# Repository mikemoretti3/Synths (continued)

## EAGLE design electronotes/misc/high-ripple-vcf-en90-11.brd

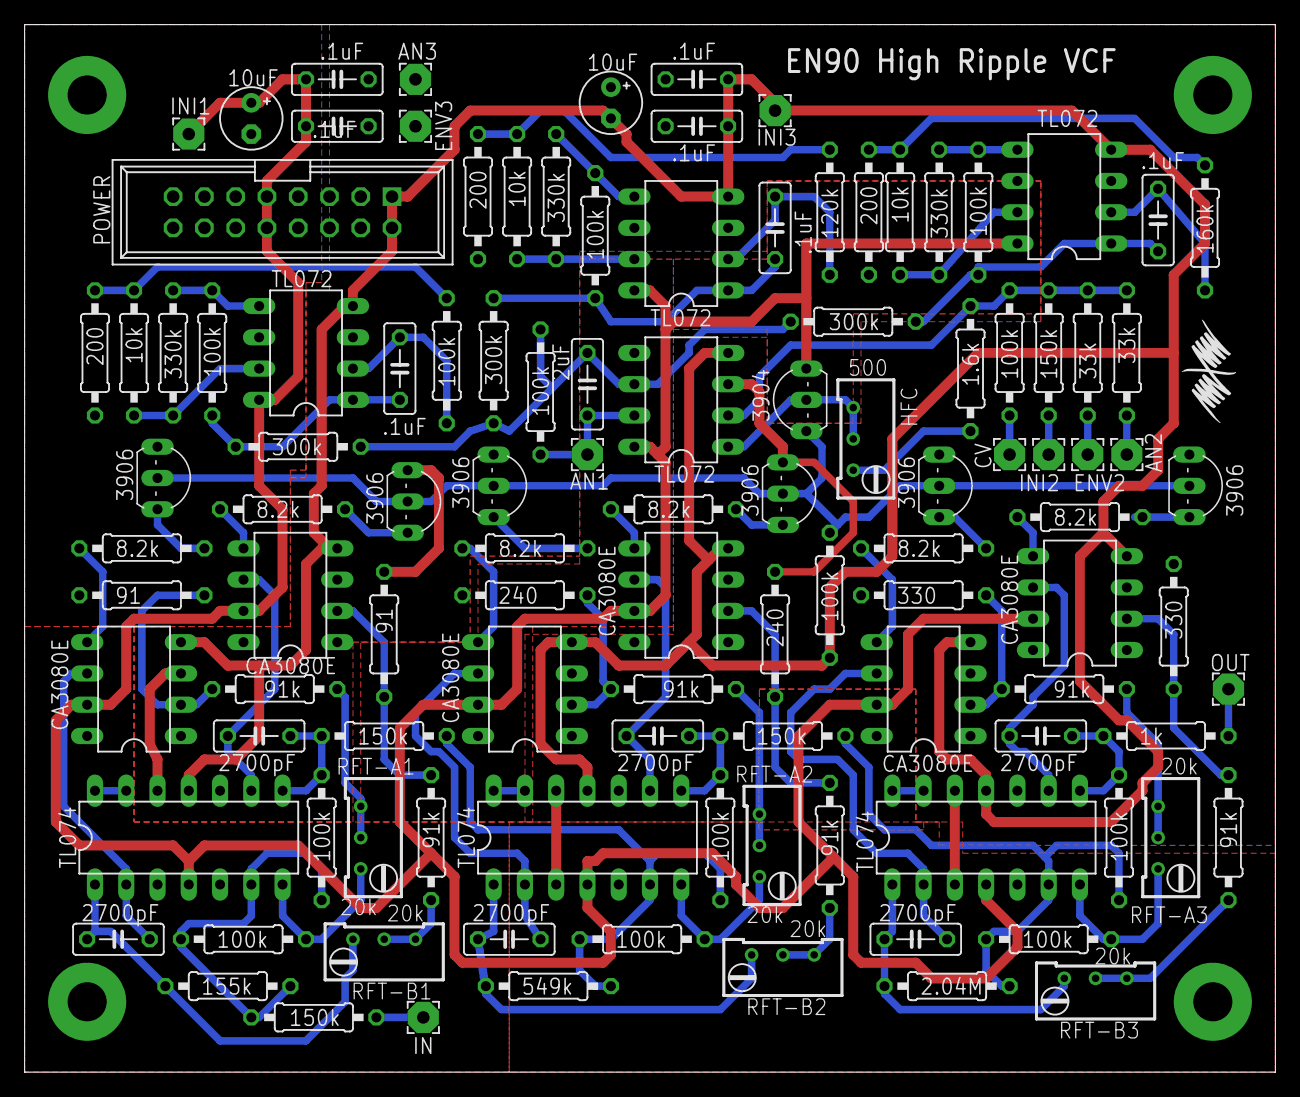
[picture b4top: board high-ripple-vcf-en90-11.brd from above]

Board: 2 copper layers, 101.6 x 85.1 mm, 111 parts (0 on the bottom side), 75 nets.

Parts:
AN1, AN2, AN3: 2,54/1,0
C1, C2, C3, C4, C9, C11, C12: .1uF; C050-025X075
C5, C6: 10uF; E2,5-5
C7, C8, C13, C14, C15, C16: 2700pF; C050-025X075
C10: 2uF; C050-025X075
CV: 2,54/1,0
ENV2, ENV3: 2,54/1,0
HFC: 500; RTRIM64W
IC1, IC8, IC11: TL074; DIL14
IC2, IC3, IC6, IC7: TL072; DIL08
IC4, IC5, IC9, IC10, IC12, IC13: CA3080E; DIL08
IN: 2,54/1,0
INI1, INI2, INI3: 2,54/1,0
OUT: 2,54/1,0
POWER: EURORACK-POWER; PINSHRD_PTH_2X8
R1, R12, R14, R16, R19, R20, R25, R29, R34, R39, R41, R44: 100k; 0207/10
R2, R13, R17, R40: 150k; 0207/10
R3, R5: 33k; 0207/10
R4: 1.6k; 0207/10
R6, R7, R8, R9, R10, R11: 8.2k; 0207/10
R15, R18, R27, R28, R42, R43: 91k; 0207/10
R21, R30, R35: 330k; 0207/10
R22, R31, R36: 10k; 0207/10
R23, R32, R37: 200; 0207/10
R24, R33, R38: 300k; 0207/10
R45: 1k; 0207/10
RA-A1: 91; 0207/10
RA-A2: 240; 0207/10
RA-A3: 330; 0207/10
RA-B1: 91; 0207/10
RA-B2: 240; 0207/10
RA-B3: 330; 0207/10
RFT-A1, RFT-A2, RFT-A3: 20k; RTRIM64W
RFT-B1, RFT-B2, RFT-B3: 20k; RTRIM64W
RQ1: 155k; 0207/10
RQ2: 549k; 0207/10
RQ3: 2.04M; 0207/10
RT1: 100k; 0207/10
RT2: 120k; 0207/10
RT3: 160k; 0207/10
T1: 3904; TO92-EBC
T2, T3, T4, T5, T6, T7: 3906; TO92-EBC

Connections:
+12V: C1.1, C3.1, C5.+, IC1.4, IC2.8, IC3.8, IC4.7, IC5.7, IC6.8, IC7.8, IC8.4, IC9.7, IC10.7, IC11.4, IC12.7, IC13.7, INI1.1, POWER.+12V@1, POWER.+12V@2, T1.C
-12V: C2.2, C4.2, C6.-, IC1.11, IC2.4, IC3.4, IC4.4, IC5.4, IC6.4, IC7.4, IC8.11, IC9.4, IC10.4, IC11.11, IC12.4, IC13.4, INI3.1, POWER.-12V@1, POWER.-12V@2, R12.1
A: IC4.5, R6.1
B: IC5.5, R7.1
C: IC9.5, R8.1
D: IC10.5, R9.1
E: IC12.5, R10.1
GND: AN3.1, C1.2, C2.1, C3.2, C4.1, C5.-, C6.+, ENV3.1, IC1.3, IC1.5, IC1.10, IC1.12, IC2.3, IC2.5, IC3.3, IC3.6, IC4.3, IC5.3, IC6.3, IC6.6, IC7.3, IC7.6, IC8.3, IC8.5, IC8.10, IC8.12, IC9.3, IC10.3, IC11.3, IC11.5, IC11.10, IC11.12, IC12.3, IC13.3, POWER.GND@1, POWER.GND@2, POWER.GND@3, POWER.GND@4, POWER.GND@5, POWER.GND@6, R23.2, R32.2, R37.2, RA-A1.1, RA-A2.1, RA-A3.1, RA-B1.1, RA-B2.1, RA-B3.1, T2.E, T3.E, T4.E, T5.E, T6.E, T7.E
unnamed: C10.1, IC2.6, R24.2, R25.1, R33.2, R38.2
unnamed: CV.1, R1.1
unnamed: INI2.1, R2.1
unnamed: ENV2.1, R3.1
unnamed: AN2.1, R5.2
unnamed: IC2.2, R1.2, R2.2, R3.2, R4.1, R5.1
unnamed: HFC.3, R4.2
unnamed: HFC.1, HFC.2, IC2.1, T1.B
unnamed: R12.2, T1.E, T2.B, T3.B, T4.B, T5.B, T6.B, T7.B
unnamed: R6.2, T2.C
unnamed: R7.2, T3.C
unnamed: R8.2, T4.C
unnamed: R9.2, T5.C
unnamed: R10.2, T6.C
unnamed: R11.2, T7.C
unnamed: C9.2, IC3.1, R20.2, R24.1
unnamed: IC3.5, R20.1, R21.2
unnamed: IC3.7, R21.1, R22.2
unnamed: R22.1, R23.1, RT1.2
unnamed: C11.2, IC6.1, R29.2, R33.1
unnamed: C9.1, IC3.2, RT1.1
unnamed: IC6.5, R29.1, R30.2
unnamed: IC6.7, R30.1, R31.2
unnamed: R31.1, R32.1, RT2.2
unnamed: C11.1, IC6.2, RT2.1
unnamed: C12.2, IC7.1, R34.2, R38.1
unnamed: IC7.5, R34.1, R35.2
unnamed: IC7.7, R35.1, R36.2
unnamed: R36.1, R37.1, RT3.2
unnamed: C12.1, IC7.2, RT3.1
unnamed: C8.2, IC1.8, R16.1, R17.1
unnamed: IC8.7, R19.2, RFT-A2.3
unnamed: R27.1, RFT-A2.1, RFT-A2.2
unnamed: IC9.2, R27.2, RA-A2.2
unnamed: C13.1, IC8.2, IC9.6
unnamed: IC1.7, R14.2, RFT-A1.3
unnamed: R15.1, RFT-A1.1, RFT-A1.2
unnamed: IC4.2, R15.2, RA-A1.2
unnamed: C7.1, IC1.2, IC4.6
unnamed: C7.2, IC1.1, RFT-B1.3, RQ1.1
unnamed: C13.2, IC8.1, RFT-B2.3, RQ2.1
unnamed: R18.2, RFT-B1.1, RFT-B1.2
unnamed: IC5.2, R18.1, RA-B1.2
unnamed: C8.1, IC1.9, IC5.6
unnamed: IC1.6, R13.2, R14.1, R16.2, RQ1.2
unnamed: IC1.13, IC1.14
unnamed: R28.2, RFT-B2.1, RFT-B2.2
unnamed: IC10.2, R28.1, RA-B2.2
unnamed: C14.1, IC8.9, IC10.6
unnamed: IC8.6, R17.2, R19.1, R39.2, RQ2.2
unnamed: IC8.13, IC8.14
unnamed: C14.2, IC8.8, R39.1, R40.1
unnamed: IC11.7, R41.2, RFT-A3.3
unnamed: R42.1, RFT-A3.1, RFT-A3.2
unnamed: IC12.2, R42.2, RA-A3.2
unnamed: C15.1, IC11.2, IC12.6
unnamed: C15.2, IC11.1, RFT-B3.3, RQ3.1
unnamed: R43.2, RFT-B3.1, RFT-B3.2
unnamed: IC13.2, R43.1, RA-B3.2
unnamed: C16.1, IC11.9, IC13.6
unnamed: IC11.6, R40.2, R41.1, R44.2, RQ3.2
unnamed: IC11.13, IC11.14
unnamed: C16.2, IC11.8, R44.1, R45.1
unnamed: IN.1, R13.1
unnamed: OUT.1, R45.2
unnamed: IC13.5, R11.1
X: AN1.1, C10.2, IC2.7, R25.2

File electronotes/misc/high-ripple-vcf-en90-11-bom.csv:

Qty,Value,Device,Package,Parts,Description
7,.1uF,C-US050-025X075,C050-025X075,"C1, C2, C3, C4, C9, C11, C12","CAPACITOR, American symbol"
6,2700pF,C-US050-025X075,C050-025X075,"C7, C8, C13, C14, C15, C16","CAPACITOR, American symbol"
1,2uF,C-US050-025X075,C050-025X075,C10,"CAPACITOR, American symbol"
2,10uF,CPOL-USE2.5-5,"E2,5-5","C5, C6","POLARIZED CAPACITOR, American symbol"
2,91,R-US_0207/10,0207/10,"RA-A1, RA-B1","RESISTOR, American symbol"
3,200,R-US_0207/10,0207/10,"R23, R32, R37","RESISTOR, American symbol"
2,240,R-US_0207/10,0207/10,"RA-A2, RA-B2","RESISTOR, American symbol"
2,330,R-US_0207/10,0207/10,"RA-A3, RA-B3","RESISTOR, American symbol"
1,1k,R-US_0207/10,0207/10,R45,"RESISTOR, American symbol"
1,1.6k,R-US_0207/10,0207/10,R4,"RESISTOR, American symbol"
6,8.2k,R-US_0207/10,0207/10,"R6, R7, R8, R9, R10, R11","RESISTOR, American symbol"
3,10k,R-US_0207/10,0207/10,"R22, R31, R36","RESISTOR, American symbol"
6,20k,R-TRIMM64W,RTRIM64W,"RFT-A1, RFT-A2, RFT-A3, RFT-B1, RFT-B2, RFT-B3",Trimm resistor
2,33k,R-US_0207/10,0207/10,"R3, R5","RESISTOR, American symbol"
6,91k,R-US_0207/10,0207/10,"R15, R18, R27, R28, R42, R43","RESISTOR, American symbol"
13,100k,R-US_0207/10,0207/10,"R1, R12, R14, R16, R19, R20, R25, R29, R34, R39, R41, R44, RT1","RESISTOR, American symbol"
1,120k,R-US_0207/10,0207/10,RT2,"RESISTOR, American symbol"
4,150k,R-US_0207/10,0207/10,"R2, R13, R17, R40","RESISTOR, American symbol"
1,155k,R-US_0207/10,0207/10,RQ1,"RESISTOR, American symbol"
1,160k,R-US_0207/10,0207/10,RT3,"RESISTOR, American symbol"
1,2.04M,R-US_0207/10,0207/10,RQ3,"RESISTOR, American symbol"
3,300k,R-US_0207/10,0207/10,"R24, R33, R38","RESISTOR, American symbol"
3,330k,R-US_0207/10,0207/10,"R21, R30, R35","RESISTOR, American symbol"
1,549k,R-US_0207/10,0207/10,RQ2,"RESISTOR, American symbol"
1,3904,2N3904-NPN-TO92-EBC,TO92-EBC,T1,NPN Transistror
6,3906,2N3906-PNP-TO92-EBC,TO92-EBC,"T2, T3, T4, T5, T6, T7",PNP Transistror
1,500,R-TRIMM64W,RTRIM64W,HFC,Trimm resistor
6,CA3080E,CA3080E,DIL08,"IC4, IC5, IC9, IC10, IC12, IC13",OTA
4,TL072,TL072-TOPP,DIL08,"IC2, IC3, IC6, IC7",OP AMP
3,TL074,TL074-TOPP,DIL14,"IC1, IC8, IC11",OP AMP
1,EURORACK-POWER,EURORACK-POWER,PINSHRD_PTH_2X8,POWER,

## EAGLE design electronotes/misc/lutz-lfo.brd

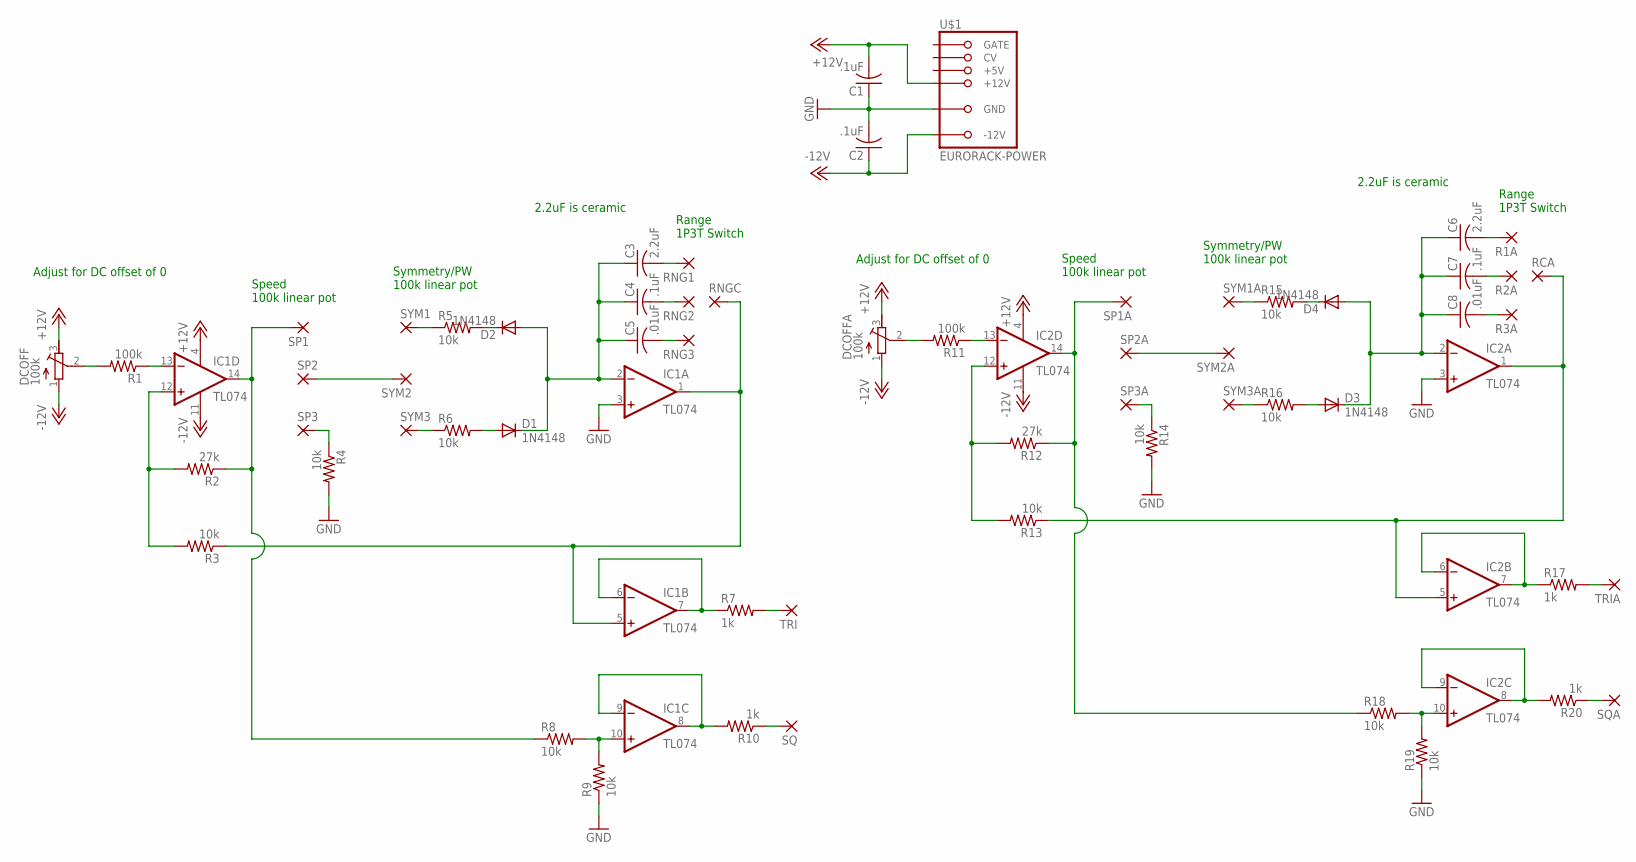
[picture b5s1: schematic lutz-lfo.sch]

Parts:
C1, C2, C4, C7: .1uF; C050-025X075
C3, C6: 2.2uF; C050-025X075
C5, C8: .01uF; C050-025X075
D1, D2, D3, D4: 1N4148; DO35-7
DCOFF: 100k; RTRIM64Y
DCOFFA: 100k; RTRIM64Y
IC1, IC2: TL074; DIL14
R1, R11: 100k; 0207/10
R1A, R2A, R3A: 2,54/1,0
R2, R12: 27k; 0207/10
R3, R4, R5, R6, R8, R9, R13, R14, R15, R16, R18, R19: 10k; 0207/10
R7, R10, R17, R20: 1k; 0207/10
RCA: 2,54/1,0
RNG1, RNG2, RNG3: 2,54/1,0
RNGC: 2,54/1,0
SP1, SP1A, SP2, SP2A, SP3, SP3A: 2,54/1,0
SQ: 2,54/1,0
SQA: 2,54/1,0
SYM1, SYM1A, SYM2, SYM2A, SYM3, SYM3A: 2,54/1,0
TRI: 2,54/1,0
TRIA: 2,54/1,0
U$1: EURORACK-POWER; PINSHRD_PTH_2X8

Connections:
+12V: C1.2, DCOFF.3 (E), DCOFFA.3 (E), IC1.4 (V+), IC2.4 (V+), U$1.+12V@1 (+12V), U$1.+12V@2 (+12V)
-12V: C2.1, DCOFF.1 (A), DCOFFA.1 (A), IC1.11 (V-), IC2.11 (V-), U$1.-12V@1 (-12V), U$1.-12V@2 (-12V)
GND: C1.1, C2.2, IC1.3 (+IN), IC2.3 (+IN), R4.2, R9.1, R14.2, R19.1, U$1.GND@1 (GND), U$1.GND@2 (GND), U$1.GND@3 (GND), U$1.GND@4 (GND), U$1.GND@5 (GND), U$1.GND@6 (GND)
unnamed: DCOFF.2 (S), R1.2
unnamed: IC1.13 (-IN), R1.1
unnamed: IC1.12 (+IN), R2.2, R3.2
unnamed: IC1.14 (OUT), R2.1, R8.1, SP1.1
unnamed: R4.1, SP3.1
unnamed: R5.1, SYM1.1
unnamed: R6.1, SYM3.1
unnamed: SP2.1, SYM2.1
unnamed: D2.C, R5.2
unnamed: D1.A, R6.2
unnamed: C3.1, C4.1, C5.1, D1.C, D2.A, IC1.2 (-IN)
unnamed: C5.2, RNG3.1
unnamed: C4.2, RNG2.1
unnamed: C3.2, RNG1.1
unnamed: IC1.1 (OUT), IC1.5 (+IN), R3.1, RNGC.1
unnamed: IC1.6 (-IN), IC1.7 (OUT), R7.1
unnamed: DCOFFA.2 (S), R11.2
unnamed: IC1.8 (OUT), IC1.9 (-IN), R10.2
unnamed: R7.2, TRI.1
unnamed: R10.1, SQ.1
unnamed: IC1.10 (+IN), R8.2, R9.2
unnamed: IC2.13 (-IN), R11.1
unnamed: IC2.12 (+IN), R12.2, R13.2
unnamed: R14.1, SP3A.1
unnamed: R15.1, SYM1A.1
unnamed: R16.1, SYM3A.1
unnamed: SP2A.1, SYM2A.1
unnamed: D4.C, R15.2
unnamed: D3.A, R16.2
unnamed: C6.1, C7.1, C8.1, D3.C, D4.A, IC2.2 (-IN)
unnamed: C8.2, R3A.1
unnamed: C7.2, R2A.1
unnamed: C6.2, R1A.1
unnamed: IC2.1 (OUT), IC2.5 (+IN), R13.1, RCA.1
unnamed: IC2.6 (-IN), IC2.7 (OUT), R17.1
unnamed: IC2.8 (OUT), IC2.9 (-IN), R20.2
unnamed: R17.2, TRIA.1
unnamed: R20.1, SQA.1
unnamed: IC2.10 (+IN), R18.2, R19.2
unnamed: IC2.14 (OUT), R12.1, R18.1, SP1A.1

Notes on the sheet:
Speed 100k linear pot
Symmetry/PW 100k linear pot
Range 1P3T Switch
2.2uF is ceramic
Adjust for DC offset of 0

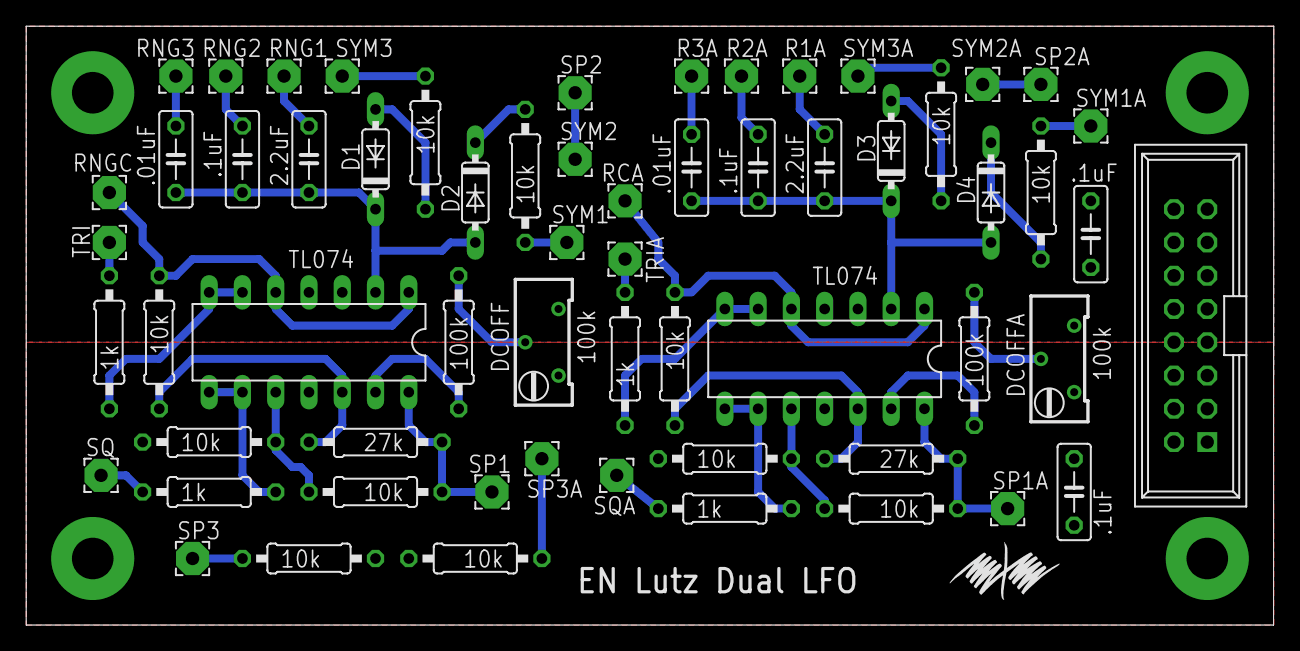
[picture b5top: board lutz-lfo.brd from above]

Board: 2 copper layers, 95.2 x 45.7 mm, 61 parts (0 on the bottom side), 43 nets.

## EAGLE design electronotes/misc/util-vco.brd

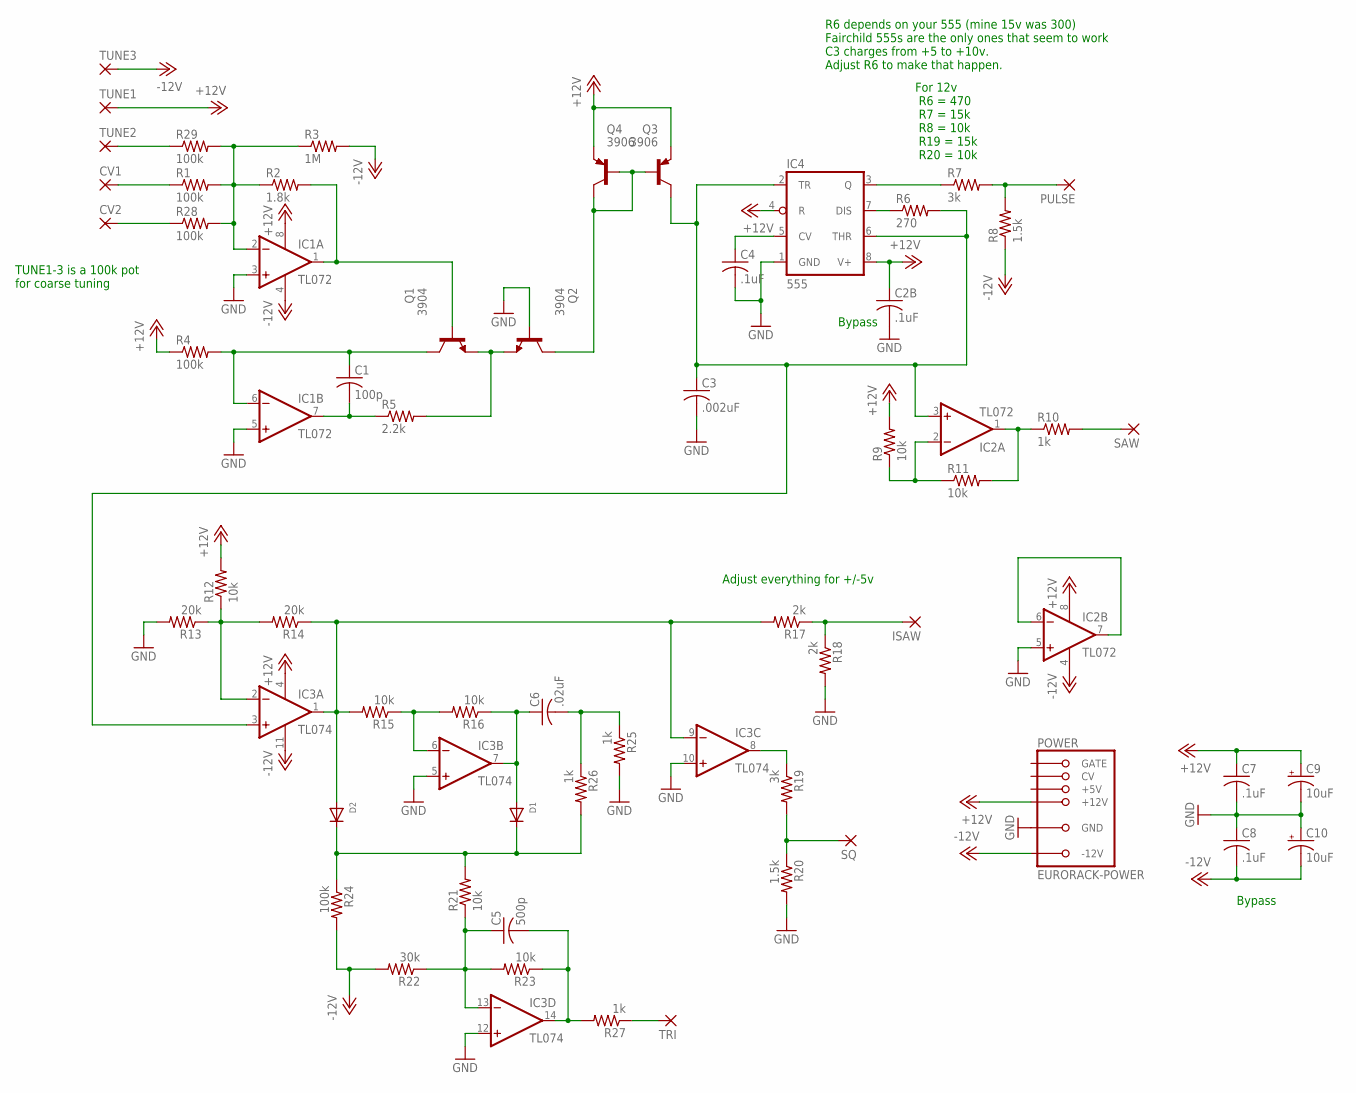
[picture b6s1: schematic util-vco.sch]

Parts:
C1: 100p; C050-025X075
C2B, C4, C7, C8: .1uF; C050-025X075
C3: .002uF; C050-025X075
C5: 500p; C050-025X075
C6: .02uF; C050-025X075
C9, C10: 10uF; E2,5-5
CV1, CV2: 2,54/1,0
D1, D2: DIODEDO-1N4148; DO-1N4148
IC1, IC2: TL072; DIL08
IC3: TL074; DIL14
IC4: 555; DIL08
ISAW: 2,54/1,0
POWER: EURORACK-POWER; PINSHRD_PTH_2X8
PULSE: 2,54/1,0
Q1, Q2: 3904; TO92
Q3, Q4: 3906; TO92
R1, R4, R24, R28, R29: 100k; 0207/10
R2: 1.8k; 0207/10
R3: 1M; 0207/10
R5: 2.2k; 0207/10
R6: 270; 0207/10
R7, R19: 3k; 0207/10
R8, R20: 1.5k; 0207/10
R9, R11, R12, R15, R16, R21, R23: 10k; 0207/10
R10, R25, R26, R27: 1k; 0207/10
R13, R14: 20k; 0207/10
R17, R18: 2k; 0207/10
R22: 30k; 0207/10
SAW: 2,54/1,0
SQ: 2,54/1,0
TRI: 2,54/1,0
TUNE1, TUNE2, TUNE3: 2,54/1,0

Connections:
+12V: C2B.1, C7.1, C9.+, IC1.8 (V+), IC2.8 (V+), IC3.4 (V+), IC4.4 (R), IC4.8 (V+), POWER.+12V@1 (+12V), POWER.+12V@2 (+12V), Q3.3 (E), Q4.3 (E), R4.1, R9.2, R12.2, TUNE1.1
-12V: C8.2, C10.-, IC1.4 (V-), IC2.4 (V-), IC3.11 (V-), POWER.-12V@1 (-12V), POWER.-12V@2 (-12V), R3.2, R8.1, R22.2, R24.2, TUNE3.1
GND: C2B.2, C3.2, C4.2, C7.2, C8.1, C9.-, C10.+, IC1.3 (+IN), IC1.5 (+IN), IC2.5 (+IN), IC3.5 (+IN), IC3.10 (+IN), IC3.12 (+IN), IC4.1 (GND), POWER.GND@1 (GND), POWER.GND@2 (GND), POWER.GND@3 (GND), POWER.GND@4 (GND), POWER.GND@5 (GND), POWER.GND@6 (GND), Q2.2 (B), R13.2, R18.2, R20.2, R25.2
unnamed: IC1.2 (-IN), R1.2, R2.1, R3.1, R28.2, R29.2
unnamed: IC1.1 (OUT), Q1.2 (B), R2.2
unnamed: C1.1, IC1.6 (-IN), Q1.1 (C), R4.2
unnamed: C1.2, IC1.7 (OUT), R5.1
unnamed: Q1.3 (E), Q2.3 (E), R5.2
unnamed: C4.1, IC4.5 (CV)
unnamed: Q2.1 (C), Q3.1 (C), Q3.2 (B), Q4.2 (B)
unnamed: D2.A, IC3.1 (OUT), IC3.9 (-IN), R14.1, R15.2, R17.2
unnamed: IC4.3 (Q), R7.1
unnamed: PULSE.1, R7.2, R8.2
unnamed: IC2.6 (-IN), IC2.7 (OUT)
unnamed: IC4.7 (DIS), R6.1
unnamed: IC3.6 (-IN), R15.1, R16.2
unnamed: C6.1, D1.A, IC3.7 (OUT), R16.1
unnamed: IC2.2 (-IN), R9.1, R11.1
unnamed: IC2.1 (OUT), R10.1, R11.2
unnamed: R10.2, SAW.1
unnamed: IC3.2 (-IN), R12.1, R13.1, R14.2
unnamed: C3.1, IC2.3 (+IN), IC3.3 (+IN), IC4.2 (TR), IC4.6 (THR), Q4.1 (C), R6.2
unnamed: C6.2, R25.1, R26.1
unnamed: D1.C, D2.C, R21.2, R24.1, R26.2
unnamed: C5.1, IC3.13 (-IN), R21.1, R22.1, R23.2
unnamed: C5.2, IC3.14 (OUT), R23.1, R27.2
unnamed: R27.1, TRI.1
unnamed: ISAW.1, R17.1, R18.1
unnamed: IC3.8 (OUT), R19.1
unnamed: R19.2, R20.1, SQ.1
unnamed: CV2.1, R28.1
unnamed: R29.1, TUNE2.1
unnamed: CV1.1, R1.1

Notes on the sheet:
Bypass
TUNE1-3 is a 100k pot for coarse tuning
Adjust everything for +/-5v
For 12v R6 = 470 R7 = 15k R8 = 10k R19 = 15k R20 = 10k
R6 depends on your 555 (mine 15v was 300) Fairchild 555s are the only ones that seem to work C3 charges from +5 to +10v. Adjust R6 to make that happen.

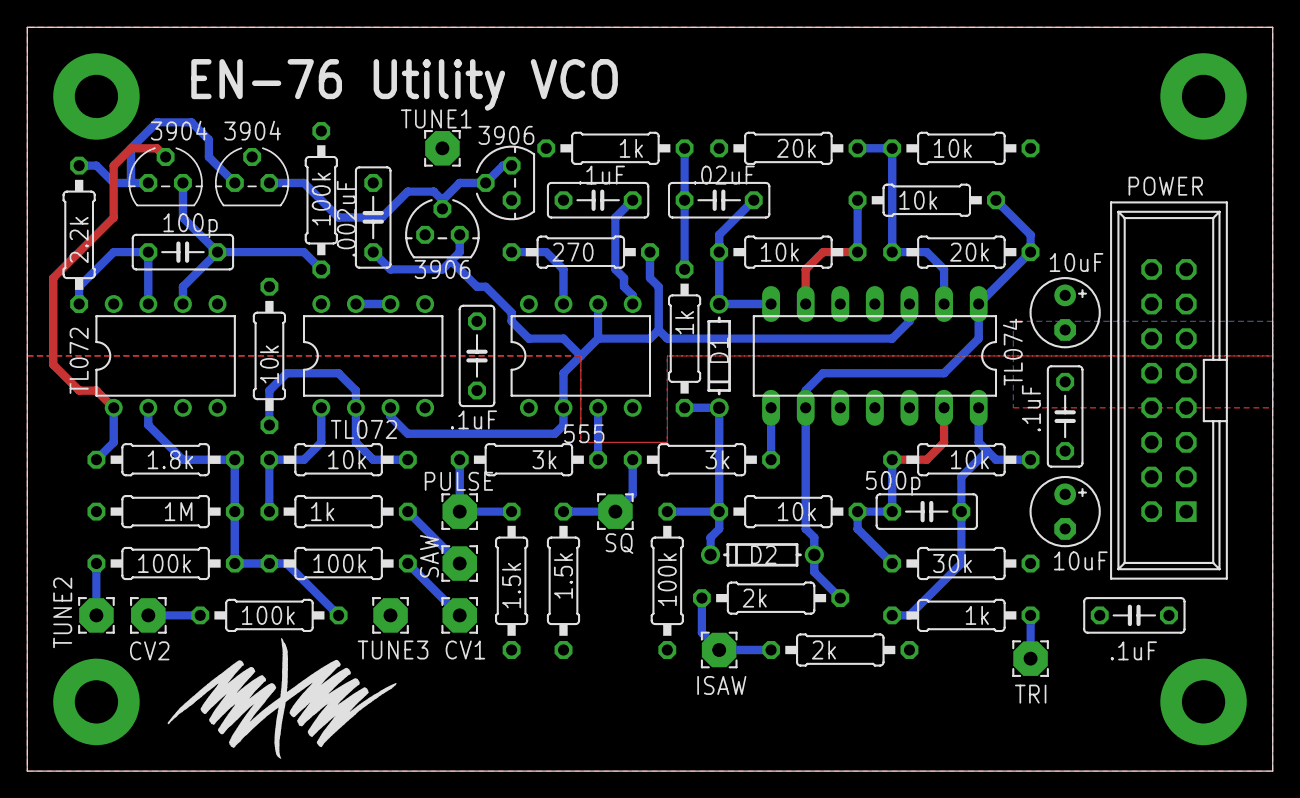
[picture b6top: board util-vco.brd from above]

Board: 2 copper layers, 91.4 x 54.6 mm, 60 parts (0 on the bottom side), 33 nets.

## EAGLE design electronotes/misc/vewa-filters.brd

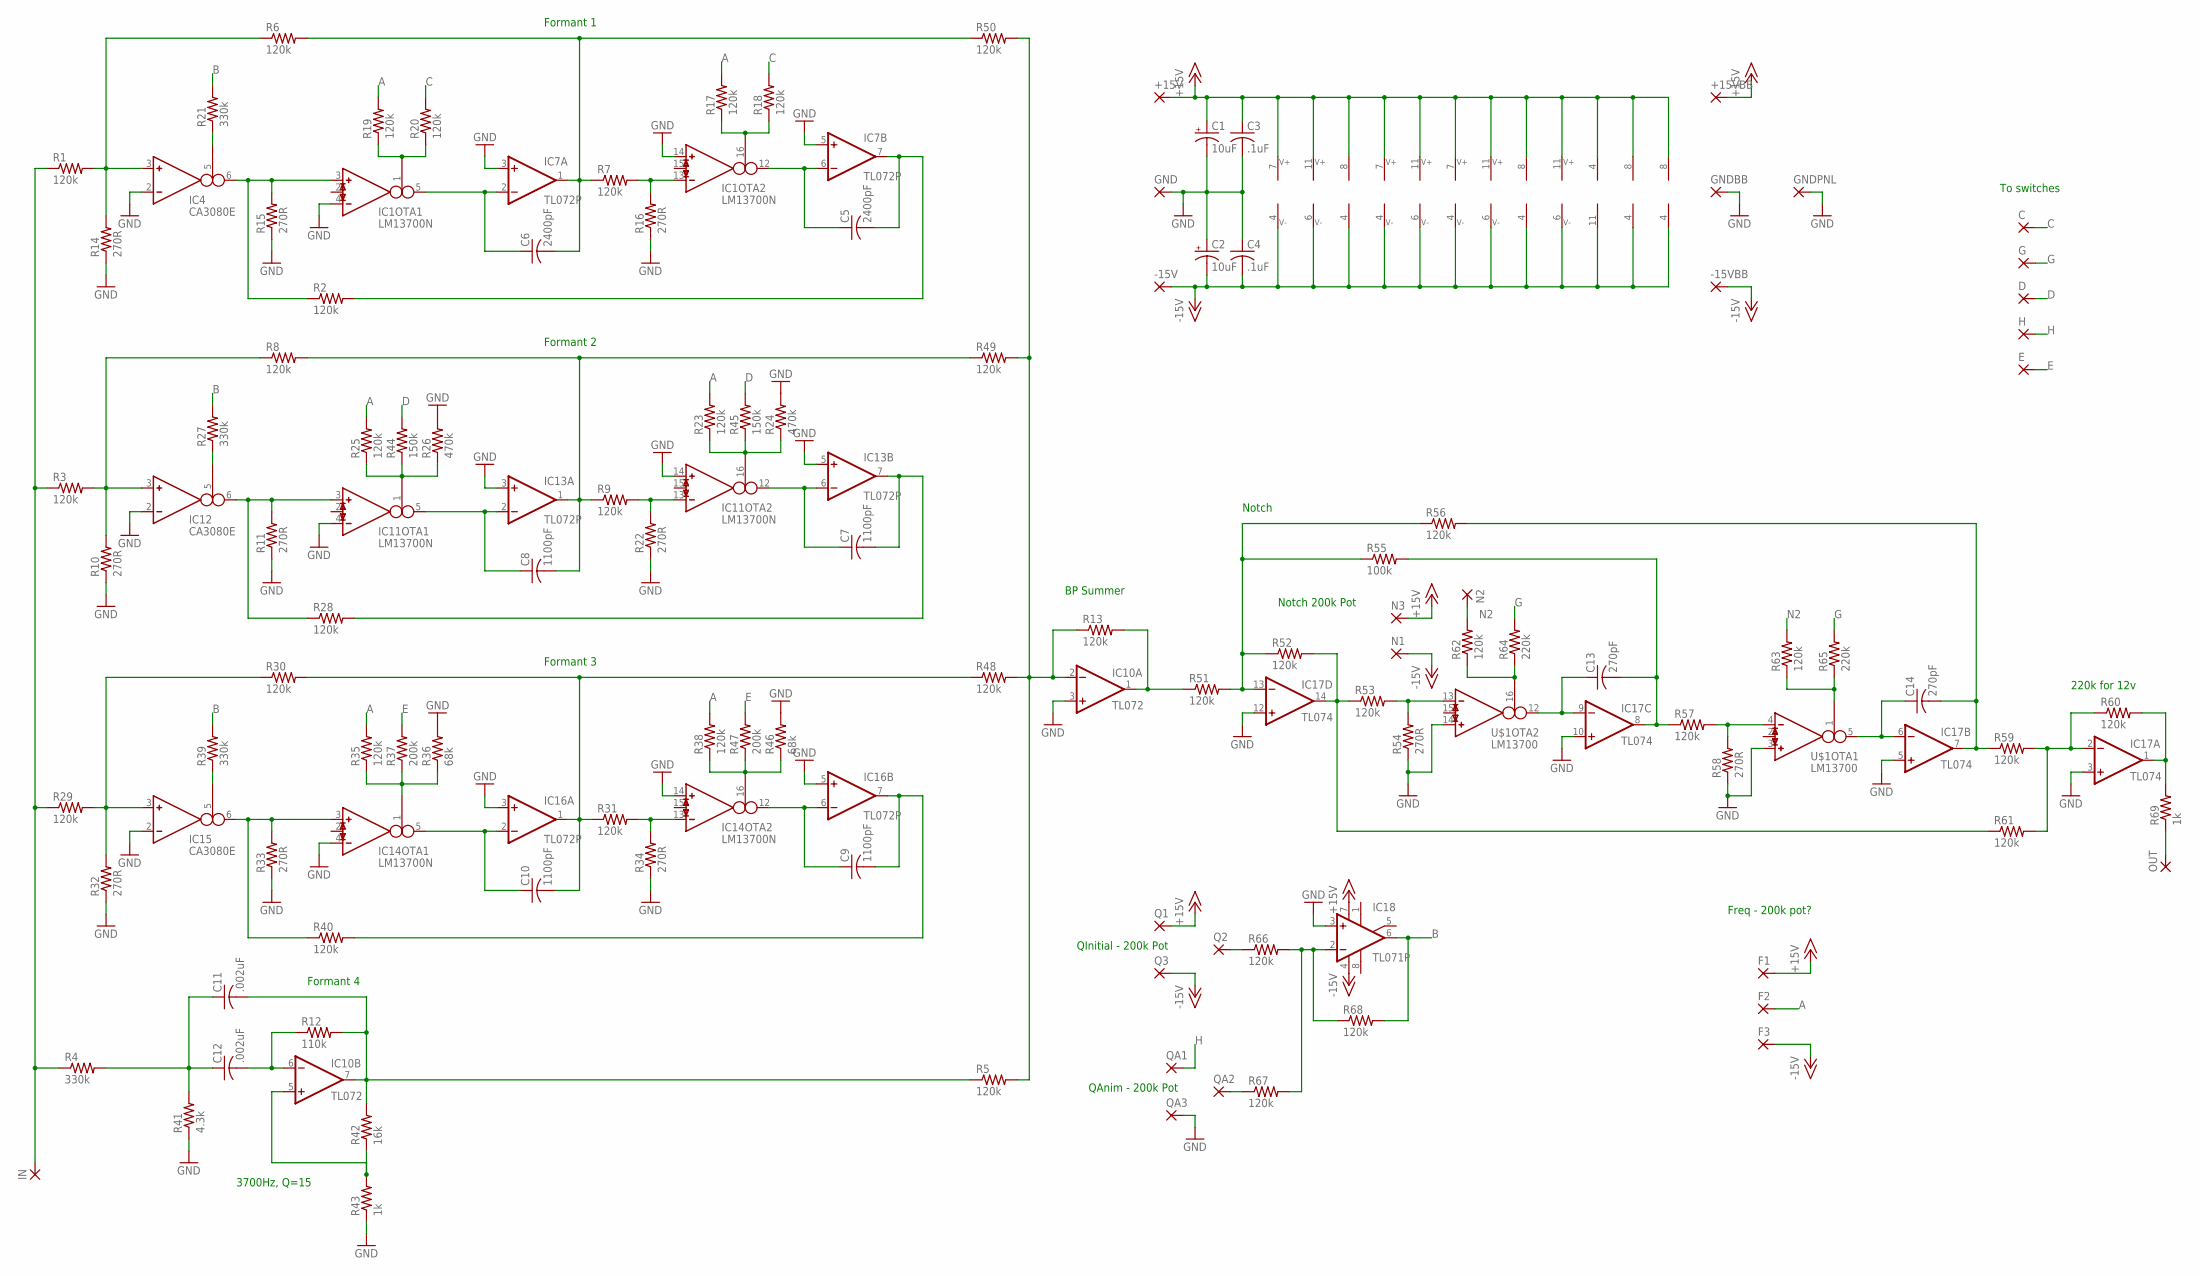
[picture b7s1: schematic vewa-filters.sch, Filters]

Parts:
+15V, +15VBB: 2,54/1,0
-15V, -15VBB: 2,54/1,0
C: 2,54/1,0
C1, C2: 10uF; E2,5-5
C3, C4: .1uF; C050-025X075
C5, C6: 2400pF; C050-025X075
C7, C8, C9, C10: 1100pF; C050-025X075
C11, C12: .002uF; C050-025X075
C13, C14: 270pF; C050-025X075
D: 2,54/1,0
E: 2,54/1,0
F1, F2, F3: 2,54/1,0
G: 2,54/1,0
GND: 2,54/1,0
GNDBB: 2,54/1,0
GNDPNL: 2,54/1,0
H: 2,54/1,0
IC1, IC11, IC14: LM13700N; DIL16
IC4, IC12, IC15: CA3080E; DIL08
IC7, IC13, IC16: TL072P; DIL08
IC10: TL072; DIL08
IC17: TL074; DIL14
IC18: TL071P; DIL08
IN: 2,54/1,0
N1, N2, N3: 2,54/1,0
OUT: 2,54/1,0
Q1, Q2, Q3: 2,54/1,0
QA1, QA2, QA3: 2,54/1,0
R1, R2, R3, R5, R6, R7, R8, R9, R13, R17, R18, R19, R20, R23, R25, R28, R29, R30, R31, R35, R38, R40, R48, R49, R50, R51, R52, R53, R56, R57, R59, R60, R61, R62, R63, R66, R67, R68: 120k; 0207/10
R4, R21, R27, R39: 330k; 0207/10
R10, R11, R14, R15, R16, R22, R32, R33, R34, R54, R58: 270R; 0207/10
R12: 110k; 0207/10
R24, R26: 470k; 0207/10
R36, R46: 68k; 0207/10
R37, R47: 200k; 0207/10
R41: 4.3k; 0207/10
R42: 16k; 0207/10
R43, R69: 1k; 0207/10
R44, R45: 150k; 0207/10
R55: 100k; 0207/10
R64, R65: 220k; 0207/10
U$1: LM13700; DIL16

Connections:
+15V: +15V.1, +15VBB.1, C1.+, C3.1, F1.1, IC1.11 (7), IC4.7, IC7.8 (V+), IC10.8 (V+), IC11.11 (7), IC12.7, IC13.8 (V+), IC14.11 (7), IC15.7, IC16.8 (V+), IC17.4 (V+), IC18.7 (V+), N3.1, Q1.1, U$1.11 (7)
-15V: -15V.1, -15VBB.1, C2.-, C4.2, F3.1, IC1.6 (4), IC4.4, IC7.4 (V-), IC10.4 (V-), IC11.6 (4), IC12.4, IC13.4 (V-), IC14.6 (4), IC15.4, IC16.4 (V-), IC17.11 (V-), IC18.4 (V-), N1.1, Q3.1, U$1.6 (4)
A: F2.1, R17.2, R19.2, R23.2, R25.2, R35.2, R38.2
B: IC18.6 (OUT), R21.2, R27.2, R39.2, R68.2
C: C.1, R18.2, R20.2
D: D.1, R44.2, R45.2
E: E.1, R37.2, R47.2
G: G.1, R64.2, R65.2
GND: C1.-, C2.+, C3.2, C4.1, GND.1, GNDBB.1, GNDPNL.1, IC1.4 (IN_N), IC1.14 (IN_P), IC4.2 (IN_N), IC7.3 (+IN), IC7.5 (+IN), IC10.3 (+IN), IC11.4 (IN_N), IC11.14 (IN_P), IC12.2 (IN_N), IC13.3 (+IN), IC13.5 (+IN), IC14.4 (IN_N), IC14.14 (IN_P), IC15.2 (IN_N), IC16.3 (+IN), IC16.5 (+IN), IC17.3 (+IN), IC17.5 (+IN), IC17.10 (+IN), IC17.12 (+IN), IC18.3 (+IN), QA3.1, R10.1, R11.1, R14.1, R15.1, R16.1, R22.1, R24.2, R26.2, R32.1, R33.1, R34.1, R36.2, R41.1, R43.1, R46.2, R54.1, R58.1, U$1.3 (IN_P), U$1.14 (IN_P)
H: H.1, QA1.1
IN: IN.1, R1.1, R3.1, R4.1, R29.1
N2: N2.1, R62.2, R63.2
unnamed: IC1.3 (IN_P), IC4.6 (OUT), R2.1, R15.2
unnamed: C6.1, IC1.5 (OUT), IC7.2 (-IN)
unnamed: IC4.3 (IN_P), R1.2, R6.1, R14.2
unnamed: IC4.5 (I_BIAS), R21.1
unnamed: IC1.13 (IN_N), R7.2, R16.2
unnamed: C11.2, IC10.7 (OUT), R5.1, R12.2, R42.2
unnamed: C6.2, IC7.1 (OUT), R6.2, R7.1, R50.1
unnamed: OUT.1, R69.1
unnamed: IC1.1 (I_BIAS), R19.1, R20.1
unnamed: C5.1, IC1.12 (OUT), IC7.6 (-IN)
unnamed: C5.2, IC7.7 (OUT), R2.2
unnamed: IC1.16 (I_BIAS), R17.1, R18.1
unnamed: IC11.3 (IN_P), IC12.6 (OUT), R11.2, R28.1
unnamed: C8.1, IC11.5 (OUT), IC13.2 (-IN)
unnamed: IC12.3 (IN_P), R3.2, R8.1, R10.2
unnamed: C8.2, IC13.1 (OUT), R8.2, R9.1, R49.1
unnamed: IC12.5 (I_BIAS), R27.1
unnamed: IC11.13 (IN_N), R9.2, R22.2
unnamed: IC11.1 (I_BIAS), R25.1, R26.1, R44.1
unnamed: IC14.1 (I_BIAS), R35.1, R36.1, R37.1
unnamed: C7.1, IC11.12 (OUT), IC13.6 (-IN)
unnamed: C7.2, IC13.7 (OUT), R28.2
unnamed: IC14.16 (I_BIAS), R38.1, R46.1, R47.1
unnamed: IC14.3 (IN_P), IC15.6 (OUT), R33.2, R40.1
unnamed: C10.1, IC14.5 (OUT), IC16.2 (-IN)
unnamed: IC15.3 (IN_P), R29.2, R30.1, R32.2
unnamed: C10.2, IC16.1 (OUT), R30.2, R31.1, R48.1
unnamed: IC15.5 (I_BIAS), R39.1
unnamed: IC14.13 (IN_N), R31.2, R34.2
unnamed: IC17.13 (-IN), R51.2, R52.1, R55.1, R56.1
unnamed: IC17.14 (OUT), R52.2, R53.1, R61.1
unnamed: C9.1, IC14.12 (OUT), IC16.6 (-IN)
unnamed: C9.2, IC16.7 (OUT), R40.2
unnamed: R53.2, R54.2, U$1.13 (IN_N)
unnamed: IC10.2 (-IN), R5.2, R13.1, R48.2, R49.2, R50.2
unnamed: IC10.1 (OUT), R13.2, R51.1
unnamed: C12.2, IC10.6 (-IN), R12.1
unnamed: IC10.5 (+IN), R42.1, R43.2
unnamed: C14.1, IC17.6 (-IN), U$1.5 (OUT)
unnamed: C14.2, IC17.7 (OUT), R56.2, R59.1
unnamed: C11.1, C12.1, R4.2, R41.2
unnamed: C13.1, IC17.9 (-IN), U$1.12 (OUT)
unnamed: C13.2, IC17.8 (OUT), R55.2, R57.1
unnamed: R57.2, R58.2, U$1.4 (IN_N)
unnamed: IC17.2 (-IN), R59.2, R60.1, R61.2
unnamed: IC17.1 (OUT), R60.2, R69.2
unnamed: Q2.1, R66.1
unnamed: R62.1, R64.1, U$1.16 (I_BIAS)
unnamed: IC18.2 (-IN), R66.2, R67.2, R68.1
unnamed: R63.1, R65.1, U$1.1 (I_BIAS)
unnamed: QA2.1, R67.1
unnamed: IC11.16 (I_BIAS), R23.1, R24.1, R45.1

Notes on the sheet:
3700Hz, Q=15
Formant 1
Formant 2
Formant 3
Notch
BP Summer
Notch 200k Pot
QInitial - 200k Pot
QAnim - 200k Pot
Formant 4
To switches
Freq - 200k pot?
220k for 12v

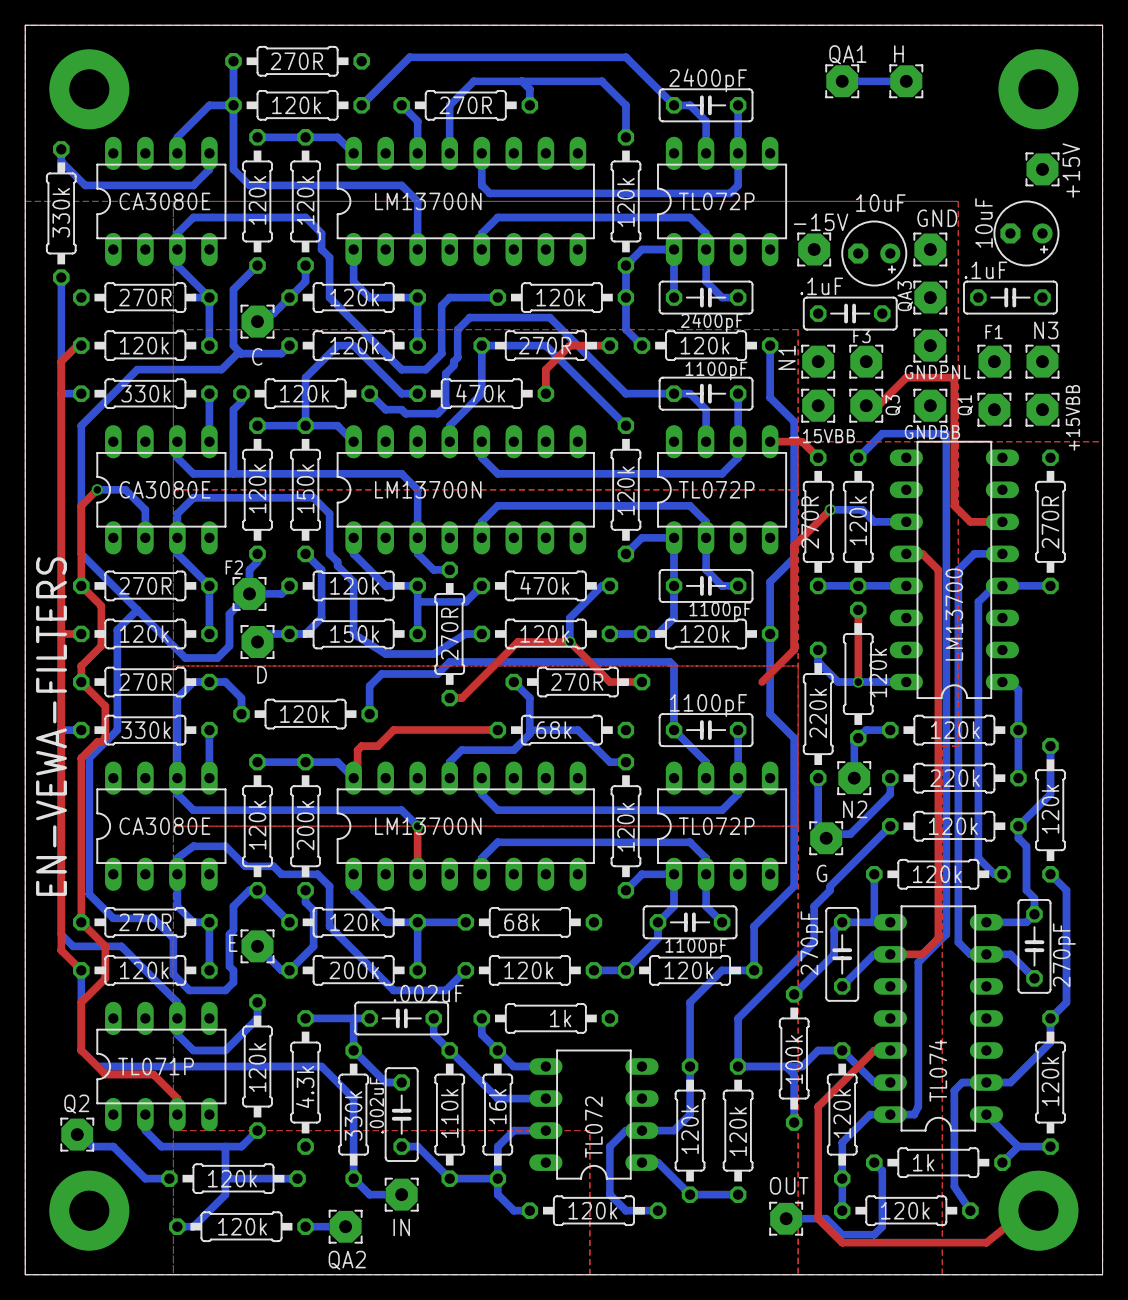
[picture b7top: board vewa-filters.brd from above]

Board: 2 copper layers, 85.4 x 99.1 mm, 122 parts (0 on the bottom side), 64 nets.
